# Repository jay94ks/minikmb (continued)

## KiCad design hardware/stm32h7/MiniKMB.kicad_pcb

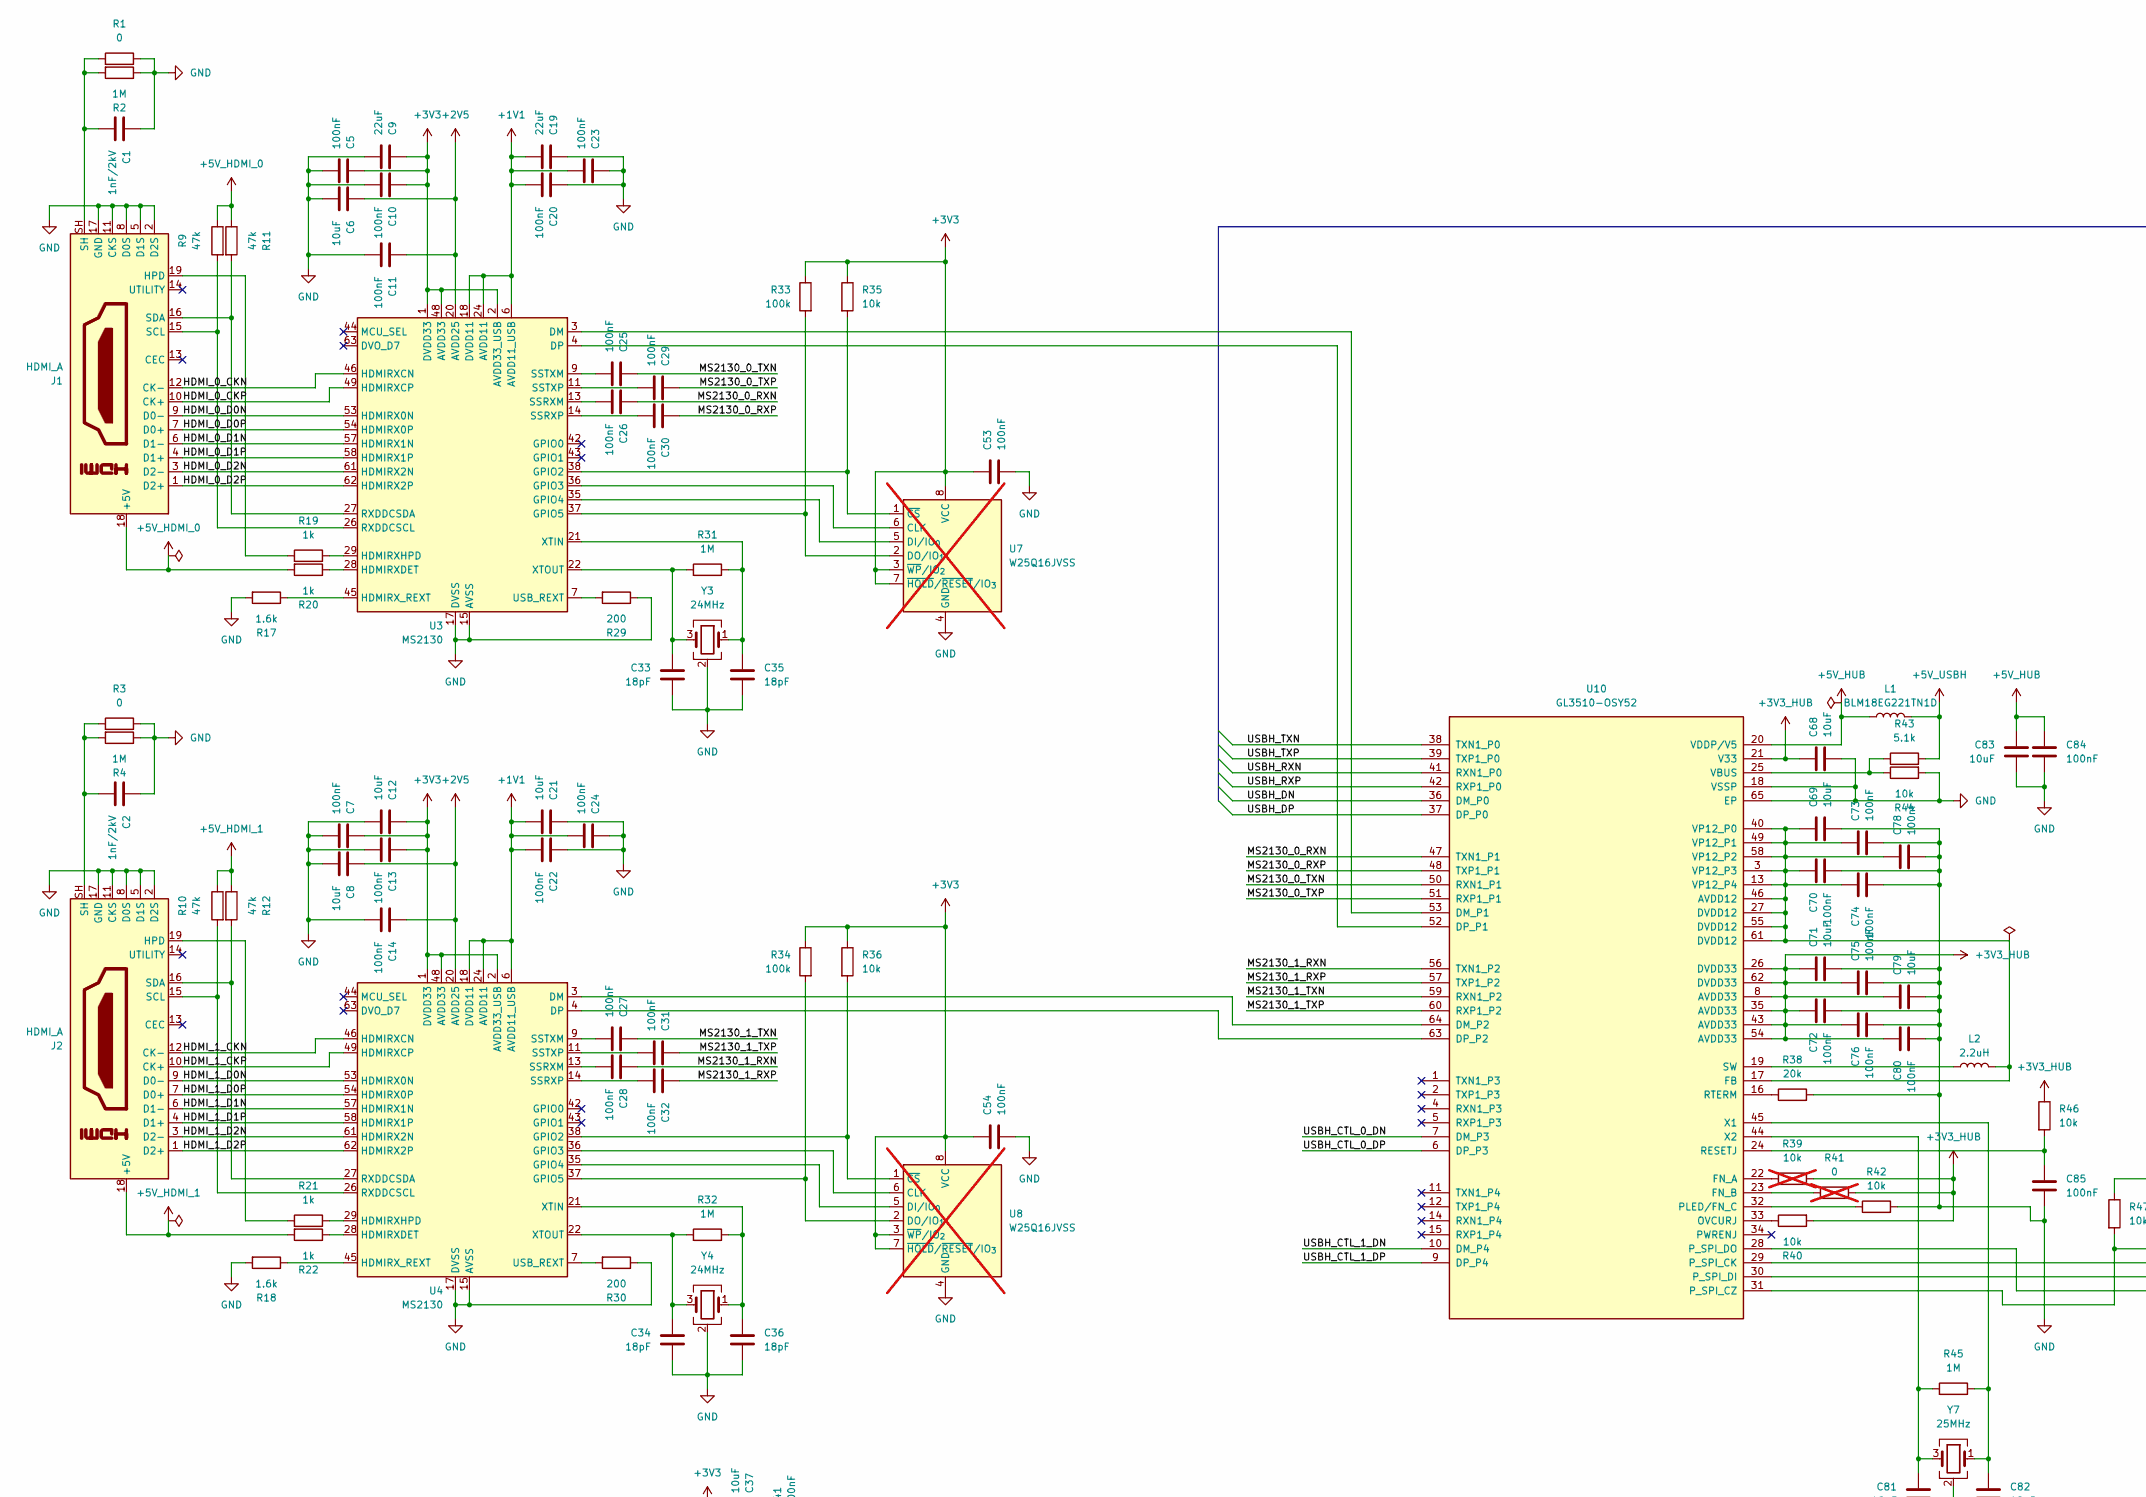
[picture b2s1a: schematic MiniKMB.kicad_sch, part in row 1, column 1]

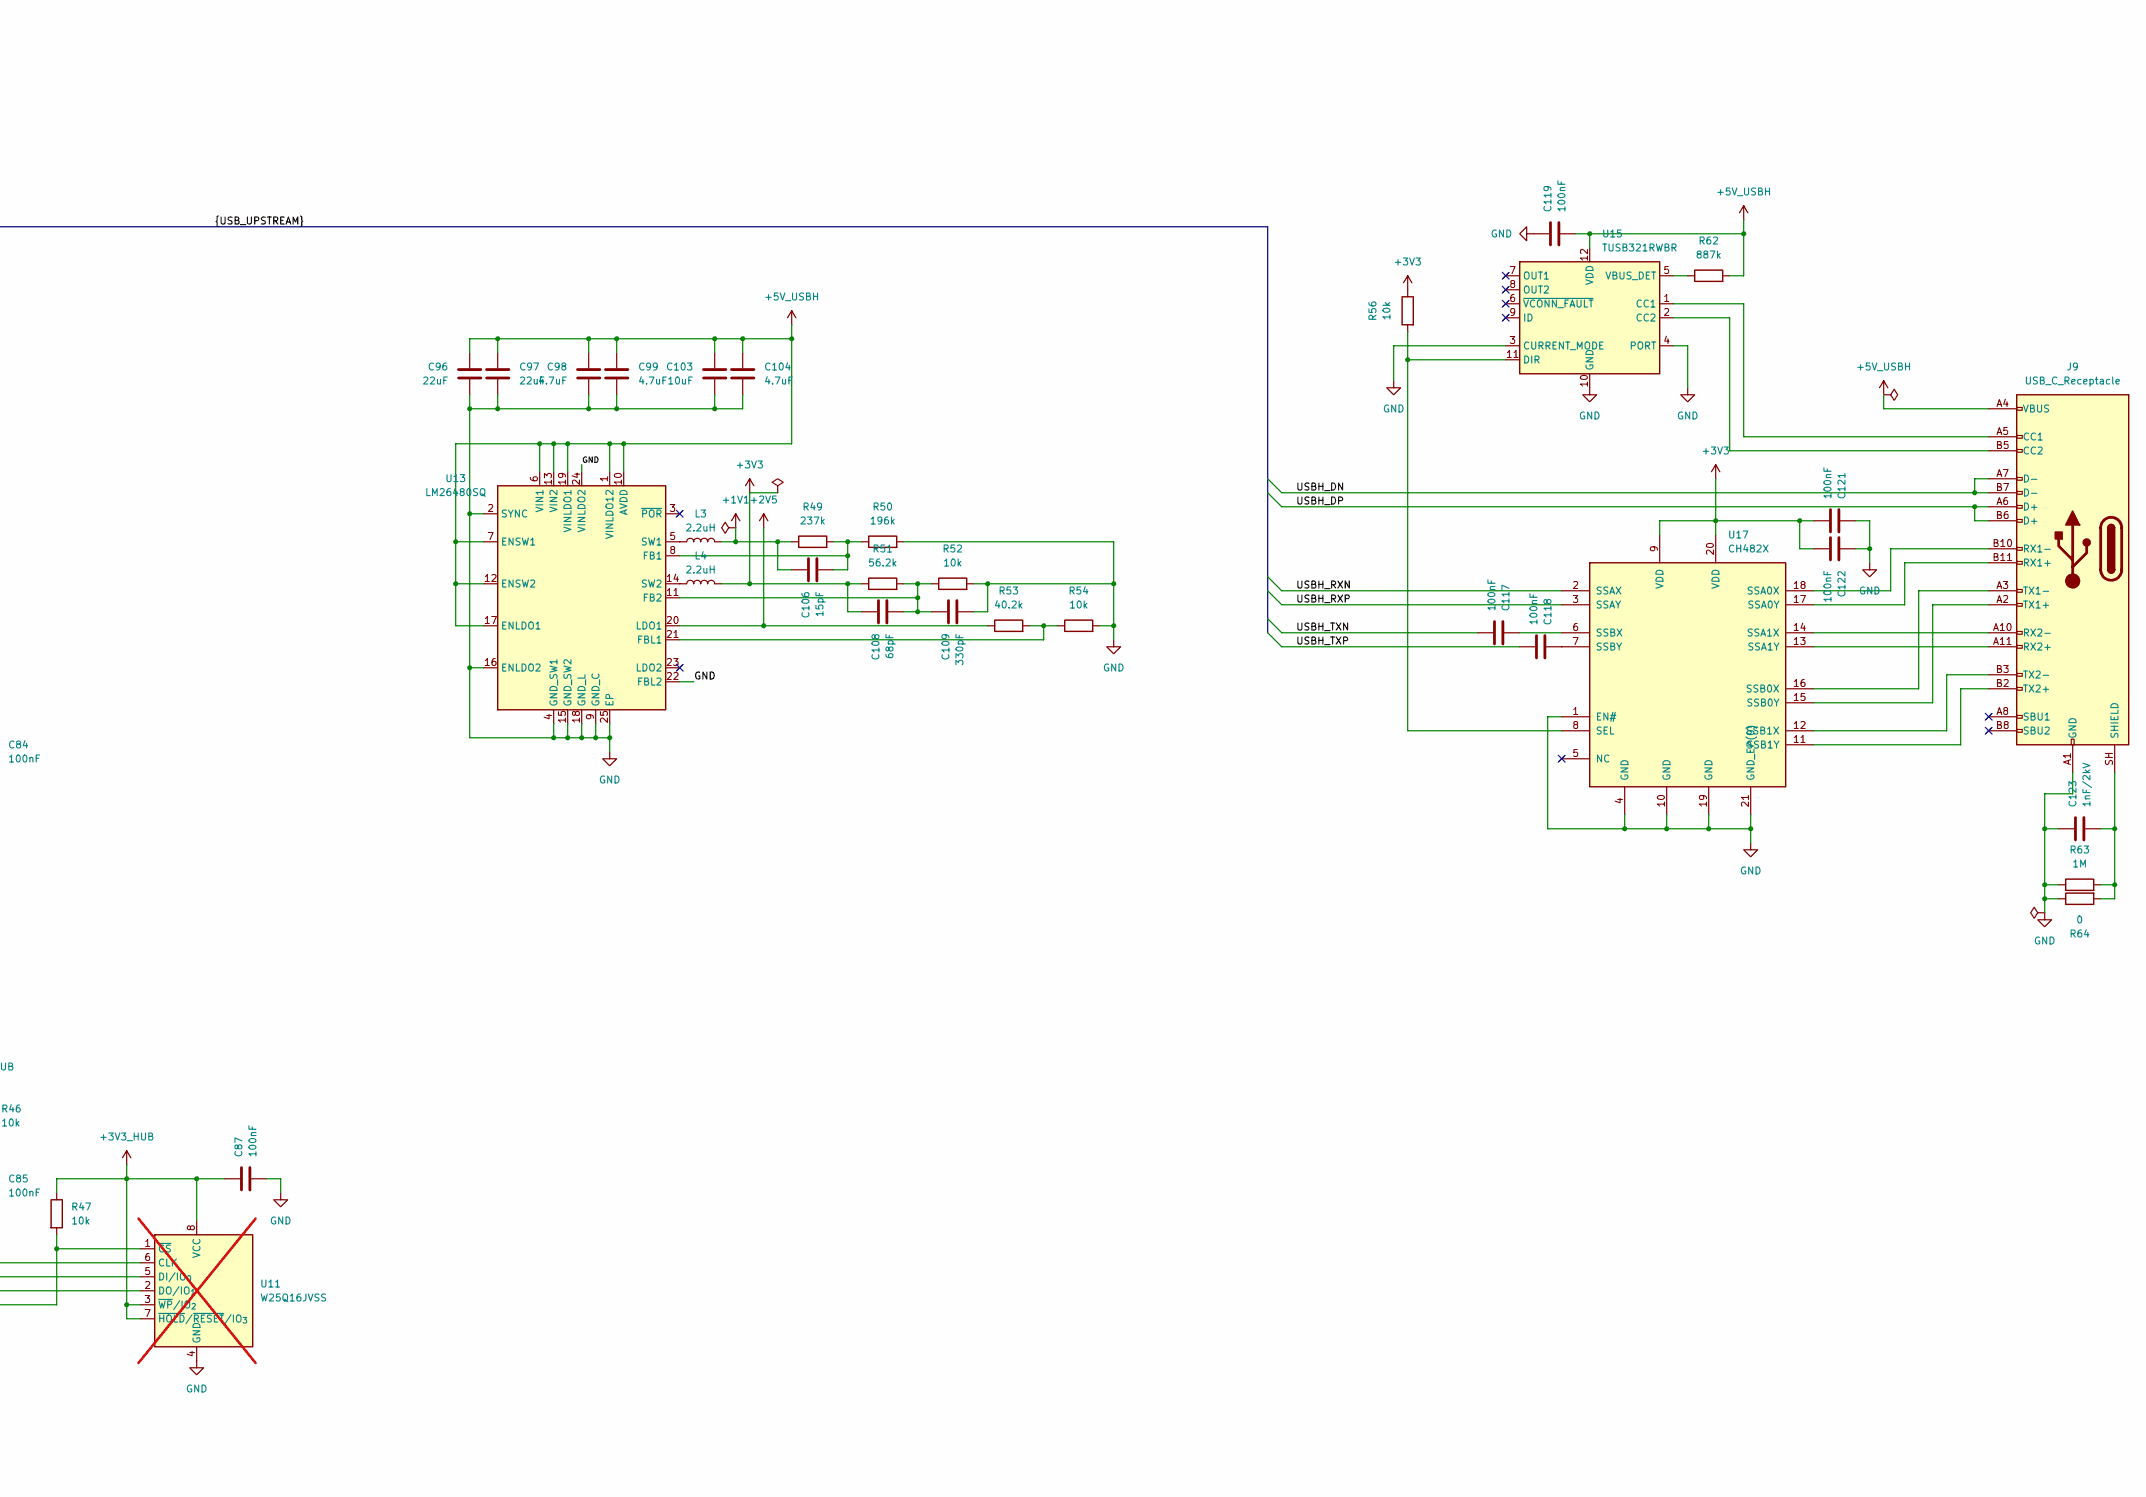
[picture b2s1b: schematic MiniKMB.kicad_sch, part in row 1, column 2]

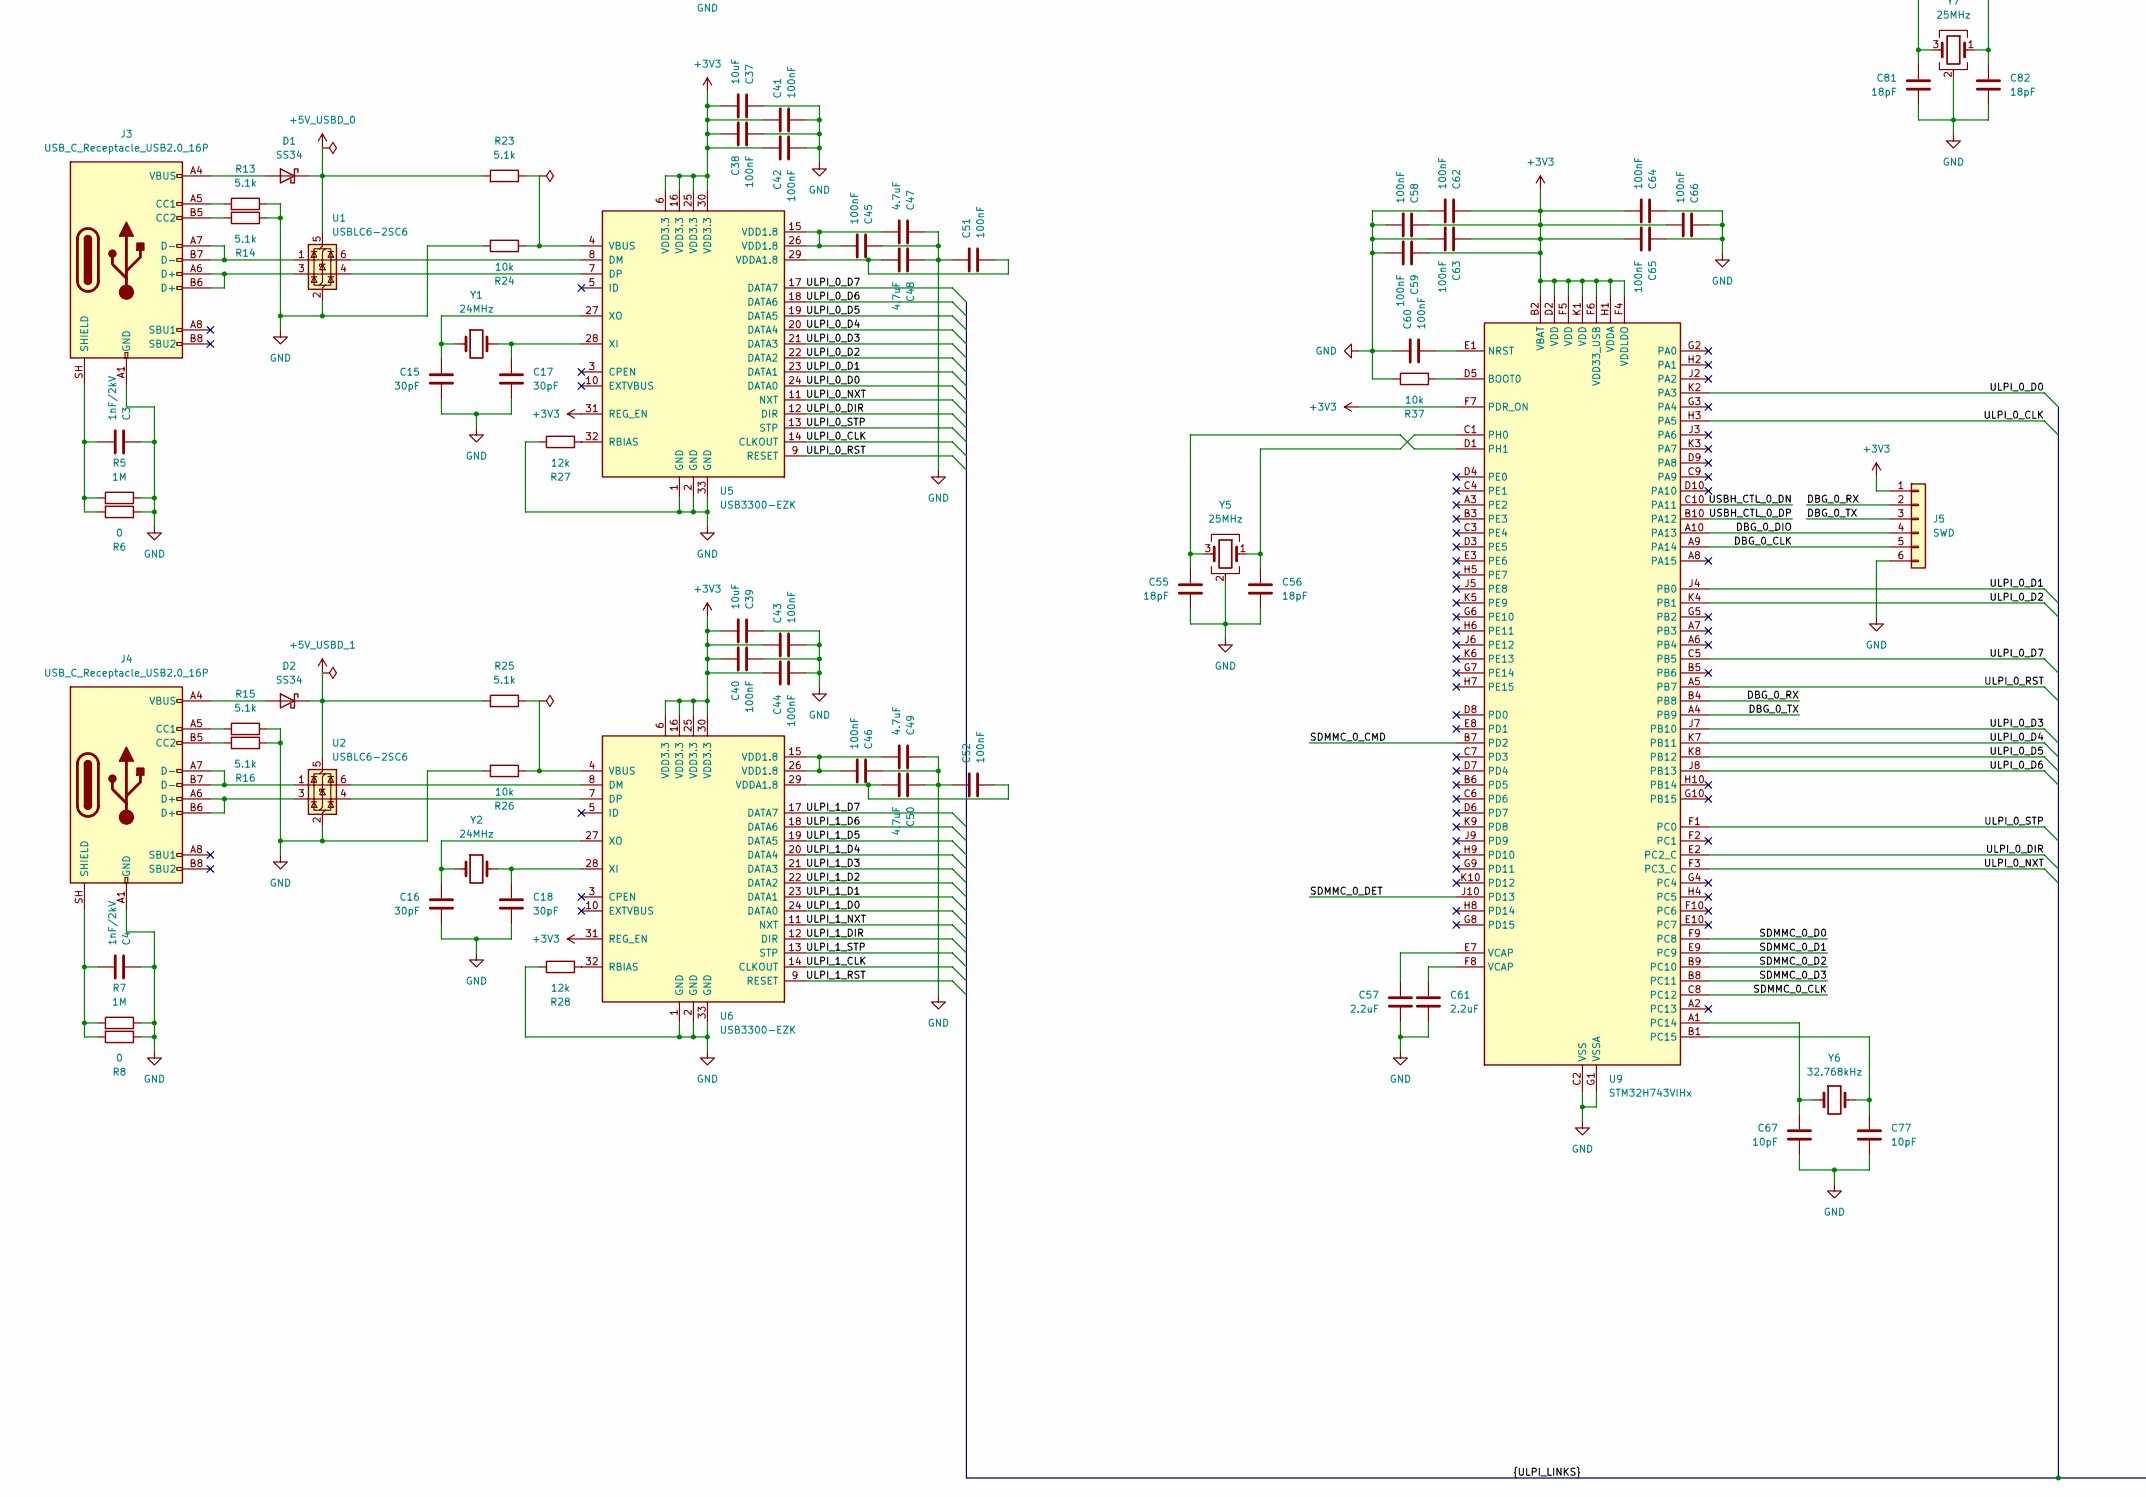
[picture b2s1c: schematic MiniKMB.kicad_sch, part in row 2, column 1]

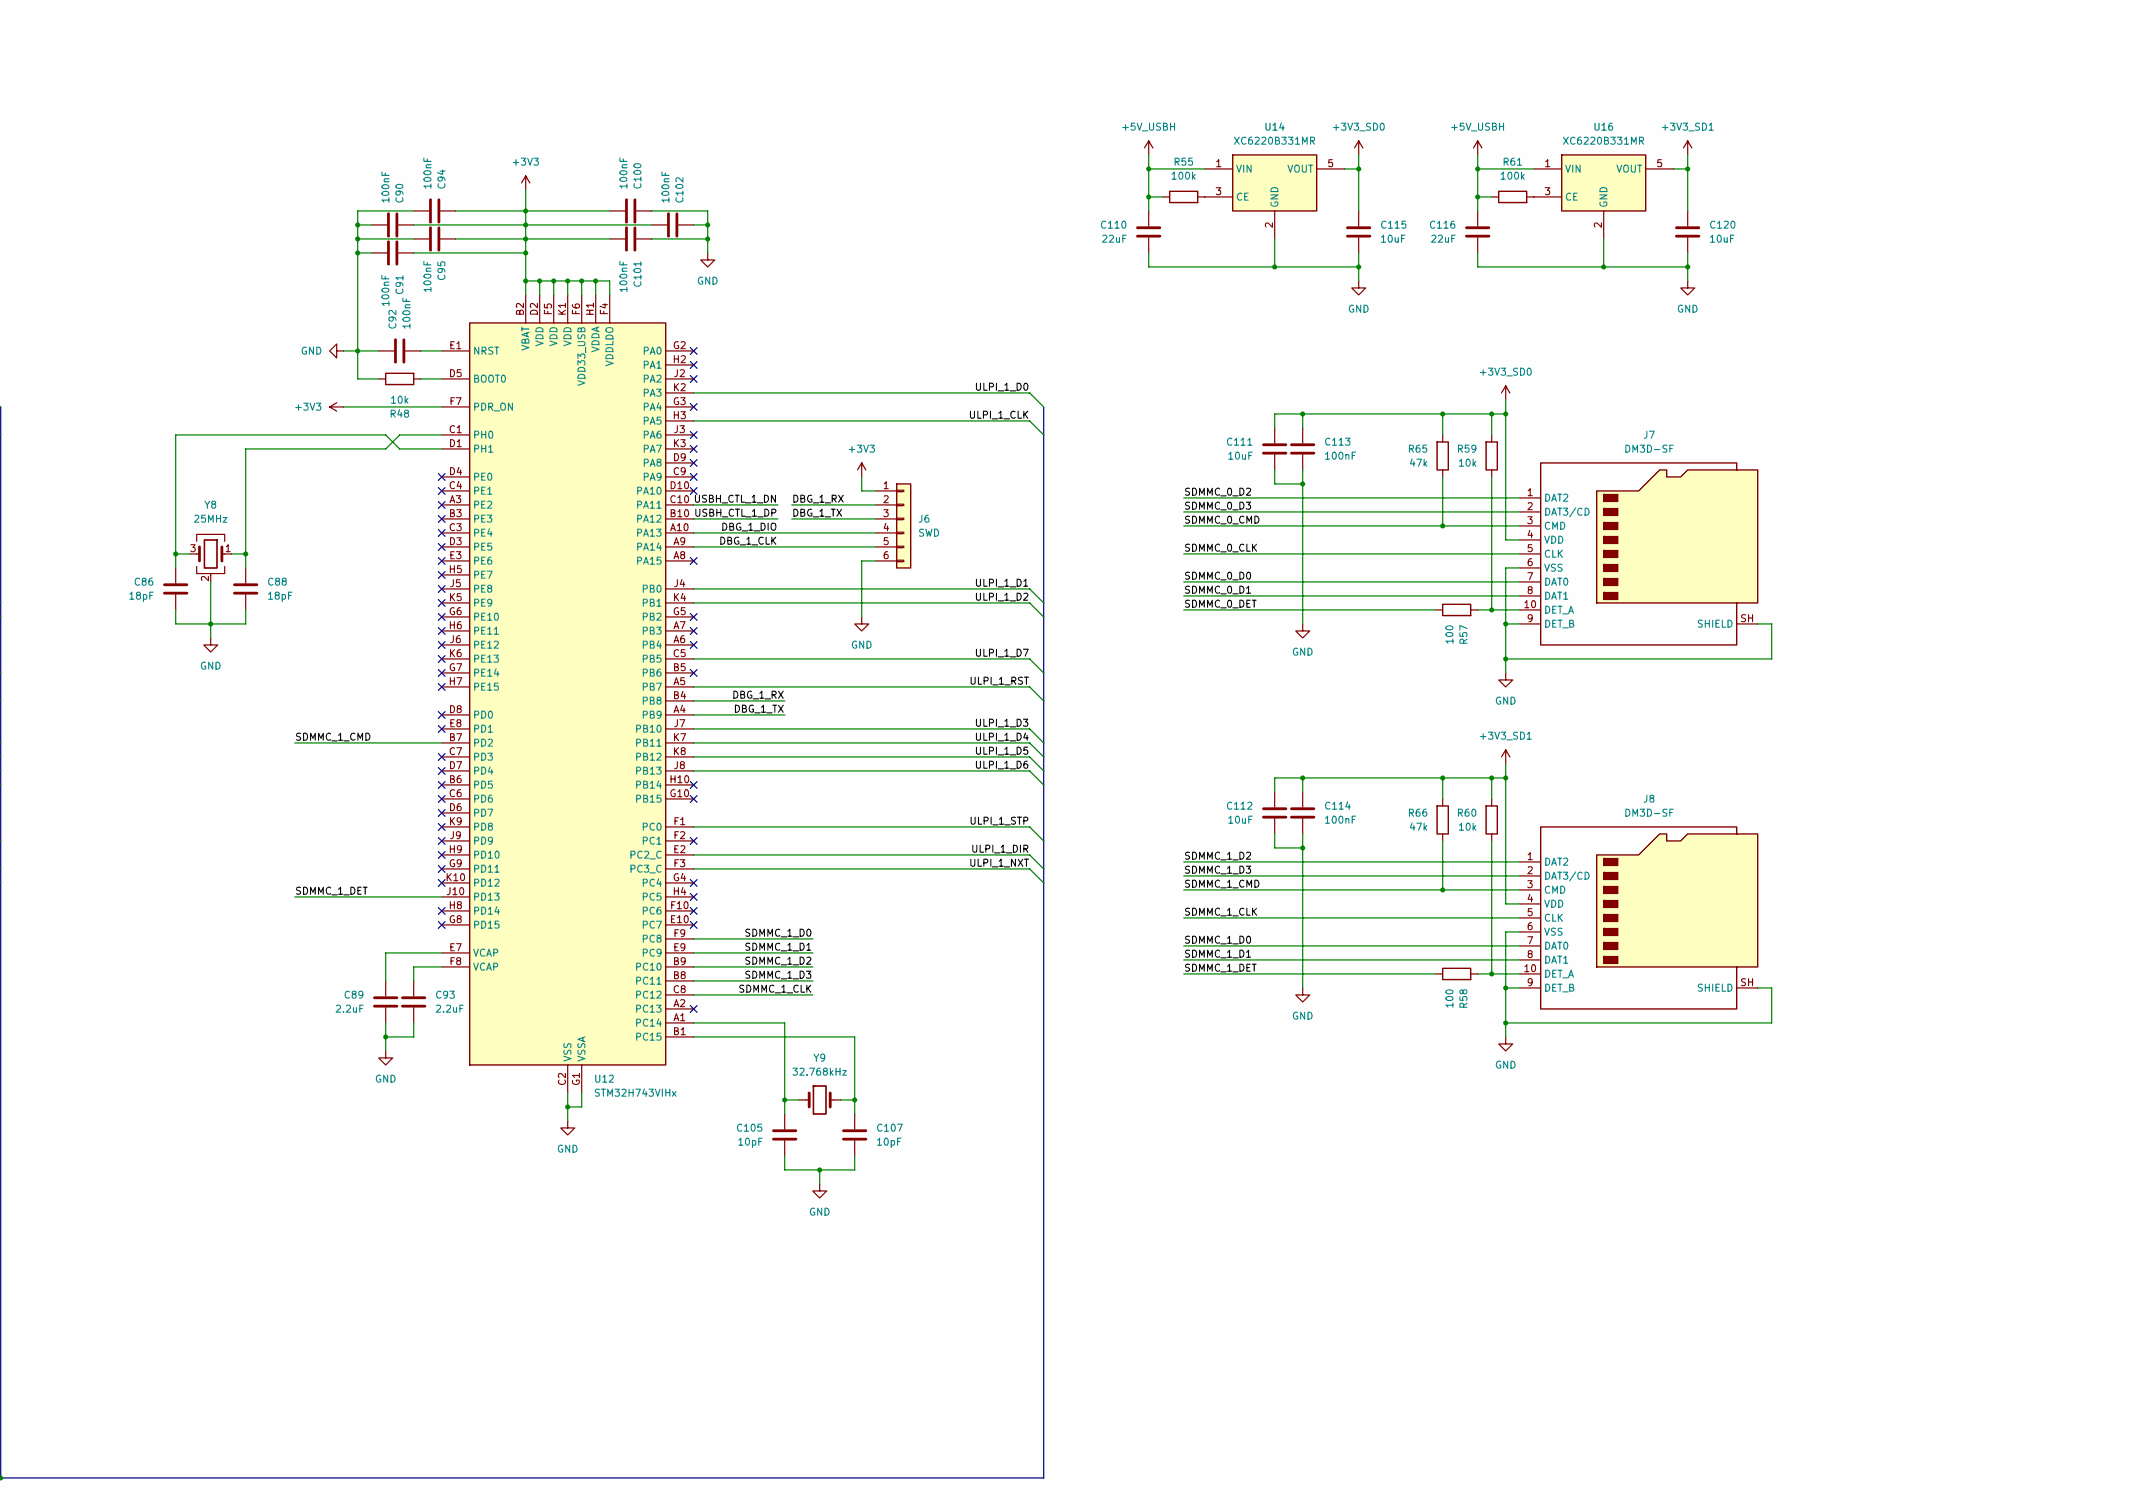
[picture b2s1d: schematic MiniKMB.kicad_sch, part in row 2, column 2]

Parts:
C1, C2, C3, C4, C123: 1nF/2kV; C_1206_3216Metric; Tolerance 10%; Voltage 2kV; MPN 1206B102K202NT; LCSC C9196
C5, C7, C10, C11, C13, C14, C20, C22, C23, C24, C25, C26, C27, C28, C29, C30, C31, C32, C38, C40, C41, C42, C43, C44, C45, C46, C51, C52, C53, C54, C58, C59, C60, C62, C63, C64, C65, C66, C70, C72, C73, C74, C75, C76, C78, C80, C84, C85, C87, C90, C91, C92, C94, C95, C100, C101, C102, C113, C114, C117, C118, C119, C121, C122: 100nF; C_0402_1005Metric; Tolerance 10%; Voltage 16V; MPN CL05B104KO5NNNC; LCSC C1525
C6, C12, C21, C37, C39, C68, C69, C71, C103, C111, C112, C120: 10uF; C_0603_1608Metric; Tolerance 20%; Voltage 25V; MPN CL10A106MA8NRNC; LCSC C96446
C8, C115: 10uF; C_0402_1005Metric; Tolerance 20%; Voltage 10V; MPN CL05A106MP6NUN8; LCSC C3902158
C9, C19: 22uF; C_0805_2012Metric; Tolerance 20%; Voltage 25V; MPN CL21A226MAQNNNE; LCSC C45783
C15, C16, C17, C18: 30pF; C_0402_1005Metric; MPN 0402CG300J500NT; LCSC C1570
C33, C34, C35, C36, C55, C56, C81, C82, C86, C88: 18pF; C_0402_1005Metric; MPN 0402CG180J500NT; LCSC C1549
C47, C48, C49, C50, C98, C99, C104: 4.7uF; C_0603_1608Metric; Tolerance 10%; Voltage 25V; MPN CL10A475KA8NQNC; LCSC C69335
C57, C61, C89, C93: 2.2uF; C_0603_1608Metric; Tolerance 10%; Voltage 10V; MPN CL10B225KP8NNNC; LCSC C100082
C67, C77, C105, C107: 10pF; C_0402_1005Metric; MPN 0402CG100J500NT; LCSC C1545
C79, C83: 10uF; C_0805_2012Metric; Tolerance 10%; Voltage 50V; MPN CL21A106KBYQNNE; LCSC C2932476
C96, C97: 22uF; C_1206_3216Metric; Tolerance 10%; Voltage 25V; MPN CL31A226KAHNNNE; LCSC C12891
C106: 15pF; C_0402_1005Metric; Tolerance 5%; Voltage 50V; MPN 0402CG150J500NT; LCSC C1548
C108: 68pF; C_0402_1005Metric; Tolerance 5%; Voltage 50V; MPN GRM1555C1H680JA01D; LCSC C76977
C109: 330pF; C_0402_1005Metric; Tolerance 5%; Voltage 50V; MPN GRM1555C1H331JA01D; LCSC C76965
C110, C116: 22uF; C_0805_2012Metric; Tolerance 20%; Voltage 25V; MPN CL21A226MAYNNNE; LCSC C602037
D1, D2: SS34; D_SMA; MPN SS34; LCSC C8678
J1, J2: HDMI_A; HDMI_A_Molex_208658-1001_Horizontal
J3, J4: USB_C_Receptacle_USB2.0_16P; USB_C_Receptacle_Palconn_UTC16-G; MPN TYPE-C-31-M-12; LCSC C165948
J5, J6: SWD; PinHeader_1x06_P2.54mm_Vertical; MPN PZ254V-11-06P; LCSC C492405
J7, J8: DM3D-SF; microSD_HC_Hirose_DM3D-SF; MPN DM3D-SF; LCSC C719027
J9: USB_C_Receptacle; USB_C_Receptacle_Amphenol_12401610E4-2A; MPN 12401610E4#2A; LCSC C5119948
L1: BLM18EG221TN1D; L_0603_1608Metric; MPN BLM18EG221TN1D; LCSC C113025
L2, L3, L4: 2.2uH; L_Sunlord_SWPA4020S; MPN SWPA4020S2R2MT; LCSC C83423
R1, R3, R6, R8, R64: 0; R_0805_2012Metric; Tolerance jumper; MPN 0805W8F0000T5E; LCSC C17477
R2, R4, R5, R7, R63: 1M; R_0805_2012Metric; Tolerance 1%; Voltage 150V; MPN 0805W8F1004T5E; LCSC C17514
R9, R10, R11, R12, R65, R66: 47k; R_0402_1005Metric; Tolerance 1%; Voltage 50V; MPN 0402WGF4702TCE; LCSC C25792
R13, R14, R15, R16, R23, R25, R43: 5.1k; R_0402_1005Metric; Tolerance 1%; Voltage 50V; MPN 0402WGF5101TCE; LCSC C25905
R17, R18: 1.6k; R_0402_1005Metric; Tolerance 1%; Voltage 50V; MPN 0402WGF1601TCE; LCSC C4908
R19, R20, R21, R22: 1k; R_0402_1005Metric; Tolerance 1%; Voltage 50V; MPN 0402WGF1001TCE; LCSC C11702
R24, R26, R35, R36, R37, R40, R42, R44, R46, R47, R48, R56, R59, R60: 10k; R_0402_1005Metric; Tolerance 1%; Voltage 50V; MPN 0402WGF1002TCE; LCSC C25744
R27, R28: 12k; R_0402_1005Metric; Tolerance 1%; Voltage 50V; MPN 0402WGF1202TCE; LCSC C25752
R29, R30: 200; R_0402_1005Metric; Tolerance 1%; Voltage 50V; MPN 0402WGF2000TCE; LCSC C25087
R31, R32, R45: 1M; R_0402_1005Metric; Tolerance 1%; Voltage 50V; MPN 0402WGF1004TCE; LCSC C26083
R33, R34, R55, R61: 100k; R_0402_1005Metric; Tolerance 1%; Voltage 50V; MPN 0402WGF1003TCE; LCSC C25741
R38: 20k; R_0402_1005Metric; Tolerance 1%; Voltage 50V; MPN 0402WGF2002TCE; LCSC C25765
R39: 10k; R_0402_1005Metric; not fitted
R41: 0; R_0402_1005Metric; not fitted
R49: 237k; R_0402_1005Metric; Tolerance 0.1%; Voltage 50V; MPN RT0402BRD07237KL; LCSC C852654
R50: 196k; R_0402_1005Metric; Tolerance 0.1%; Voltage 50V; MPN RT0402BRD07196KL; LCSC C852585
R51: 56.2k; R_0402_1005Metric; Tolerance 0.1%; Voltage 50V; MPN RT0402BRB0756K2L; LCSC C705626
R52, R54: 10k; R_0402_1005Metric; Tolerance 0.1%; Voltage 50V; MPN RT0402BRD0710KL; LCSC C190095
R53: 40.2k; R_0402_1005Metric; Tolerance 0.1%; Voltage 50V; MPN RT0402BRD0740K2L; LCSC C852775
R57, R58: 100; R_0402_1005Metric; Tolerance 1%; Voltage 50V; MPN 0402WGF1000TCE; LCSC C25076
R62: 887k; R_0402_1005Metric; Tolerance 1%; Voltage 50V; MPN 0402WGF8873TCE; LCSC C423127
U1, U2: USBLC6-2SC6; SOT-23-6; MPN USBLC6-2SC6; LCSC C7519
U3, U4: MS2130; QFN-64-1EP_9x9mm_P0.5mm_EP5.7x5.7mm; MPN MS2130; LCSC C5905137
U5, U6: USB3300-EZK; QFN-32-1EP_5x5mm_P0.5mm_EP3.45x3.45mm; MPN USB3300-EZK-TR; LCSC C108383
U7, U8, U11: W25Q16JVSS; SOIC-8_5.3x5.3mm_P1.27mm; not fitted
U9, U12: STM32H743VIHx; TFBGA-100_8x8mm_Layout10x10_P0.8mm; MPN STM32H743VIH6; LCSC C964146
U10: GL3510-OSY52; GL3510-OSY52_QFN-64-1EP_8x8mm_P0.4mm; MPN GL3510-OSY52; LCSC C7501408
U13: LM26480SQ; WQFN-24-1EP_4x4mm_P0.5mm_EP2.6x2.6mm; MPN LM26480SQ-AA/NOPB; LCSC C131997
U14, U16: XC6220B331MR; SOT-23-5; MPN XC6220B331MR-G; LCSC C86534
U15: TUSB321RWBR; Texas_X2QFN-12_1.6x1.6mm_P0.4mm; MPN TUSB321RWBR; LCSC C139392
U17: CH482X; CH482X_QFN-20-1EP_2.5x4.5mm_P0.5mm; MPN CH482X; LCSC C2913011
Y1, Y2: 24MHz; Crystal_SMD_HC49-SD; MPN X49SS2-24.000-F18LJDT; LCSC C2890201
Y3, Y4: 24MHz; Crystal_SMD_3225-4Pin_3.2x2.5mm; MPN X322524MOB4SI; LCSC C70590
Y5, Y7, Y8: 25MHz; Crystal_SMD_3225-4Pin_3.2x2.5mm; MPN X322525MOB4SI; LCSC C9006
Y6, Y9: 32.768kHz; Crystal_SMD_2012-2Pin_2.0x1.2mm; MPN X1A0000610006; LCSC C99009

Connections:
+1V1: C19.2, C20.2, C21.2, C22.2, C23.2, C24.2, C106.1, L3.2, R49.1, U3.6 (AVDD11_USB), U3.10 (AVDD11_USB), U3.12 (AVDD11_USB), U3.18 (DVDD11), U3.24 (AVDD11), U3.39 (DVDD11), U3.51 (AVDD11), U3.55 (AVDD11), U3.59 (AVDD11), U4.6 (AVDD11_USB), U4.10 (AVDD11_USB), U4.12 (AVDD11_USB), U4.18 (DVDD11), U4.24 (AVDD11), U4.39 (DVDD11), U4.51 (AVDD11), U4.55 (AVDD11), U4.59 (AVDD11)
+2V5: C6.1, C8.1, C11.1, C14.1, R53.1, U3.20 (AVDD25), U3.23 (AVDD25), U3.47 (AVDD25), U4.20 (AVDD25), U4.23 (AVDD25), U4.47 (AVDD25), U13.20 (LDO1)
+3V3: C5.1, C7.1, C9.1, C10.1, C12.1, C13.1, C37.2, C38.1, C39.2, C40.1, C41.1, C42.1, C43.1, C44.1, C53.1, C54.1, C58.1, C59.1, C62.1, C63.1, C64.2, C65.2, C66.2, C90.1, C91.1, C94.1, C95.1, C100.2, C101.2, C102.2, C108.1, C121.2, C122.2, J5.1, J6.1, L4.2, R33.1, R34.1, R35.1, R36.1, R51.1, R56.1, U3.1 (DVDD33), U3.2 (AVDD33_USB), U3.5 (AVDD33_USB), U3.8 (AVDD33_USB), U3.16 (DVDD33), U3.31 (DVDD33), U3.33 (DVDD33), U3.41 (DVDD33), U3.48 (AVDD33), U3.52 (AVDD33), U3.56 (AVDD33), U3.60 (AVDD33), U4.1 (DVDD33), U4.2 (AVDD33_USB), U4.5 (AVDD33_USB), U4.8 (AVDD33_USB), U4.16 (DVDD33), U4.31 (DVDD33), U4.33 (DVDD33), U4.41 (DVDD33), U4.48 (AVDD33), U4.52 (AVDD33), U4.56 (AVDD33), U4.60 (AVDD33), U5.6 (VDD3.3), U5.16 (VDD3.3), U5.25 (VDD3.3), U5.30 (VDD3.3), U5.31 (REG_EN), U6.6 (VDD3.3), U6.16 (VDD3.3), U6.25 (VDD3.3), U6.30 (VDD3.3), U6.31 (REG_EN), U7.3 (~WP/IO_{2}), U7.7 (~HOLD/~RESET/IO_{3}), U7.8 (VCC), U8.3 (~WP/IO_{2}), U8.7 (~HOLD/~RESET/IO_{3}), U8.8 (VCC), U9.B2 (VBAT), U9.D2 (VDD), U9.F4 (VDDLDO), U9.F5 (VDD), U9.F6 (VDD33_USB), U9.F7 (PDR_ON), U9.H1 (VDDA), U9.K1 (VDD), U12.B2 (VBAT), U12.D2 (VDD), U12.F4 (VDDLDO), U12.F5 (VDD), U12.F6 (VDD33_USB), U12.F7 (PDR_ON), U12.H1 (VDDA), U12.K1 (VDD), U17.9 (VDD), U17.20 (VDD)
+3V3_HUB: C68.1, C71.1, C72.1, C75.1, C76.1, C79.1, C80.1, C87.1, R39.2, R40.2, R41.2, R46.1, R47.1, U10.8 (AVDD33), U10.21 (V33), U10.26 (DVDD33), U10.35 (AVDD33), U10.43 (AVDD33), U10.54 (AVDD33), U10.62 (DVDD33), U11.3 (~WP/IO_{2}), U11.7 (~HOLD/~RESET/IO_{3}), U11.8 (VCC)
+3V3_SD0: C111.1, C113.1, C115.1, J7.4 (VDD), R59.2, R65.2, U14.5 (VOUT)
+3V3_SD1: C112.1, C114.1, C120.1, J8.4 (VDD), R60.2, R66.2, U16.5 (VOUT)
+5V_HDMI_0: J1.18 (+5V), R9.1, R11.1, R20.2
+5V_HDMI_1: J2.18 (+5V), R10.1, R12.1, R22.2
+5V_HUB: C83.1, C84.1, L1.1, U10.20 (VDDP/V5)
+5V_USBD_0: D1.1 (K), R23.2, U1.5 (VBUS)
+5V_USBD_1: D2.1 (K), R25.2, U2.5 (VBUS)
+5V_USBH: C96.1, C97.1, C98.1, C99.1, C103.1, C104.1, C110.1, C116.1, C119.2, J9.A4 (VBUS), J9.A9 (VBUS), J9.B4 (VBUS), J9.B9 (VBUS), L1.2, R43.2, R55.1, R61.1, R62.2, U13.1 (VINLDO12), U13.6 (VIN1), U13.7 (ENSW1), U13.10 (AVDD), U13.12 (ENSW2), U13.13 (VIN2), U13.17 (ENLDO1), U13.19 (VINLDO1), U14.1 (VIN), U15.12 (VDD), U16.1 (VIN)
/DBG_0_CLK: J5.5, U9.A9 (PA14)
/DBG_0_DIO: J5.4, U9.A10 (PA13)
/DBG_0_RX: J5.2, U9.B4 (PB8)
/DBG_0_TX: J5.3, U9.A4 (PB9)
/DBG_1_CLK: J6.5, U12.A9 (PA14)
/DBG_1_DIO: J6.4, U12.A10 (PA13)
/DBG_1_RX: J6.2, U12.B4 (PB8)
/DBG_1_TX: J6.3, U12.A4 (PB9)
/HDMI_0_CKN: J1.12 (CK-), U3.46 (HDMIRXCN)
/HDMI_0_CKP: J1.10 (CK+), U3.49 (HDMIRXCP)
/HDMI_0_D0N: J1.9 (D0-), U3.53 (HDMIRX0N)
/HDMI_0_D0P: J1.7 (D0+), U3.54 (HDMIRX0P)
/HDMI_0_D1N: J1.6 (D1-), U3.57 (HDMIRX1N)
/HDMI_0_D1P: J1.4 (D1+), U3.58 (HDMIRX1P)
/HDMI_0_D2N: J1.3 (D2-), U3.61 (HDMIRX2N)
/HDMI_0_D2P: J1.1 (D2+), U3.62 (HDMIRX2P)
/HDMI_1_CKN: J2.12 (CK-), U4.46 (HDMIRXCN)
/HDMI_1_CKP: J2.10 (CK+), U4.49 (HDMIRXCP)
/HDMI_1_D0N: J2.9 (D0-), U4.53 (HDMIRX0N)
/HDMI_1_D0P: J2.7 (D0+), U4.54 (HDMIRX0P)
/HDMI_1_D1N: J2.6 (D1-), U4.57 (HDMIRX1N)
/HDMI_1_D1P: J2.4 (D1+), U4.58 (HDMIRX1P)
/HDMI_1_D2N: J2.3 (D2-), U4.61 (HDMIRX2N)
/HDMI_1_D2P: J2.1 (D2+), U4.62 (HDMIRX2P)
/MS2130_0_RXN: C26.1, U10.47 (TXN1_P1)
/MS2130_0_RXP: C30.1, U10.48 (TXP1_P1)
/MS2130_0_TXN: C25.1, U10.50 (RXN1_P1)
/MS2130_0_TXP: C29.1, U10.51 (RXP1_P1)
/MS2130_1_RXN: C28.1, U10.56 (TXN1_P2)
/MS2130_1_RXP: C32.1, U10.57 (TXP1_P2)
/MS2130_1_TXN: C27.1, U10.59 (RXN1_P2)
/MS2130_1_TXP: C31.1, U10.60 (RXP1_P2)
/SDMMC_0_CLK: J7.5 (CLK), U9.C8 (PC12)
/SDMMC_0_CMD: J7.3 (CMD), R65.1, U9.B7 (PD2)
/SDMMC_0_D0: J7.7 (DAT0), U9.F9 (PC8)
/SDMMC_0_D1: J7.8 (DAT1), U9.E9 (PC9)
/SDMMC_0_D2: J7.1 (DAT2), U9.B9 (PC10)
/SDMMC_0_D3: J7.2 (DAT3/CD), U9.B8 (PC11)
/SDMMC_0_DET: R57.1, U9.J10 (PD13)
/SDMMC_1_CLK: J8.5 (CLK), U12.C8 (PC12)
/SDMMC_1_CMD: J8.3 (CMD), R66.1, U12.B7 (PD2)
/SDMMC_1_D0: J8.7 (DAT0), U12.F9 (PC8)
/SDMMC_1_D1: J8.8 (DAT1), U12.E9 (PC9)
/SDMMC_1_D2: J8.1 (DAT2), U12.B9 (PC10)
/SDMMC_1_D3: J8.2 (DAT3/CD), U12.B8 (PC11)
/SDMMC_1_DET: R58.1, U12.J10 (PD13)
/ULPI_0_CLK: U5.14 (CLKOUT), U9.H3 (PA5)
/ULPI_0_D0: U5.24 (DATA0), U9.K2 (PA3)
/ULPI_0_D1: U5.23 (DATA1), U9.J4 (PB0)
/ULPI_0_D2: U5.22 (DATA2), U9.K4 (PB1)
/ULPI_0_D3: U5.21 (DATA3), U9.J7 (PB10)
/ULPI_0_D4: U5.20 (DATA4), U9.K7 (PB11)
/ULPI_0_D5: U5.19 (DATA5), U9.K8 (PB12)
/ULPI_0_D6: U5.18 (DATA6), U9.J8 (PB13)
/ULPI_0_D7: U5.17 (DATA7), U9.C5 (PB5)
/ULPI_0_DIR: U5.12 (DIR), U9.E2 (PC2_C)
/ULPI_0_NXT: U5.11 (NXT), U9.F3 (PC3_C)
/ULPI_0_RST: U5.9 (RESET), U9.A5 (PB7)
/ULPI_0_STP: U5.13 (STP), U9.F1 (PC0)
/ULPI_1_CLK: U6.14 (CLKOUT), U12.H3 (PA5)
/ULPI_1_D0: U6.24 (DATA0), U12.K2 (PA3)
/ULPI_1_D1: U6.23 (DATA1), U12.J4 (PB0)
/ULPI_1_D2: U6.22 (DATA2), U12.K4 (PB1)
/ULPI_1_D3: U6.21 (DATA3), U12.J7 (PB10)
/ULPI_1_D4: U6.20 (DATA4), U12.K7 (PB11)
/ULPI_1_D5: U6.19 (DATA5), U12.K8 (PB12)
/ULPI_1_D6: U6.18 (DATA6), U12.J8 (PB13)
/ULPI_1_D7: U6.17 (DATA7), U12.C5 (PB5)
/ULPI_1_DIR: U6.12 (DIR), U12.E2 (PC2_C)
/ULPI_1_NXT: U6.11 (NXT), U12.F3 (PC3_C)
/ULPI_1_RST: U6.9 (RESET), U12.A5 (PB7)
/ULPI_1_STP: U6.13 (STP), U12.F1 (PC0)
/USBH_CTL_0_DN: U9.C10 (PA11), U10.7 (DM_P3)
/USBH_CTL_0_DP: U9.B10 (PA12), U10.6 (DP_P3)
/USBH_CTL_1_DN: U10.10 (DM_P4), U12.C10 (PA11)
/USBH_CTL_1_DP: U10.9 (DP_P4), U12.B10 (PA12)
/USBH_DN: J9.A7 (D-), J9.B7 (D-), U10.36 (DM_P0)
/USBH_DP: J9.A6 (D+), J9.B6 (D+), U10.37 (DP_P0)
/USBH_RXN: U10.41 (RXN1_P0), U17.2 (SSAX)
/USBH_RXP: U10.42 (RXP1_P0), U17.3 (SSAY)
/USBH_TXN: C117.2, U10.38 (TXN1_P0)
/USBH_TXP: C118.2, U10.39 (TXP1_P0)
GND: C1.1, C2.1, C3.1, C4.1, C5.2, C6.2, C7.2, C8.2, C9.2, C10.2, C11.2, C12.2, C13.2, C14.2, C15.2, C16.2, C17.2, C18.2, C19.1, C20.1, C21.1, C22.1, C23.1, C24.1, C33.2, C34.2, C35.2, C36.2, C37.1, C38.2, C39.1, C40.2, C41.2, C42.2, C43.2, C44.2, C45.1, C46.1, C47.1, C48.1, C49.1, C50.1, C51.1, C52.1, C53.2, C54.2, C55.2, C56.2, C57.2, C58.2, C59.2, C60.1, C61.2, C62.2, C63.2, C64.1, C65.1, C66.1, C67.2, C68.2, C69.2, C70.2, C71.2, C72.2, C73.2, C74.2, C75.2, C76.2, C77.2, C78.2, C79.2, C80.2, C81.2, C82.2, C83.2, C84.2, C85.2, C86.2, C87.2, C88.2, C89.2, C90.2, C91.2, C92.1, C93.2, C94.2, C95.2, C96.2, C97.2, C98.2, C99.2, C100.1, C101.1, C102.1, C103.2, C104.2, C105.2, C107.2, C109.2, C110.2, C111.2, C112.2, C113.2, C114.2, C115.2, C116.2, C119.1, C120.2, C121.1, C122.1, C123.1, J1.2 (D2S), J1.5 (D1S), J1.8 (D0S), J1.11 (CKS), J1.17 (GND), J2.2 (D2S), J2.5 (D1S), J2.8 (D0S), J2.11 (CKS), J2.17 (GND), J3.A1 (GND), J3.A12 (GND), J3.B1 (GND), J3.B12 (GND), J4.A1 (GND), J4.A12 (GND), J4.B1 (GND), J4.B12 (GND), J5.6, J6.6, J7.6 (VSS), J7.9 (DET_B), J7.SH (SHIELD), J8.6 (VSS), J8.9 (DET_B), J8.SH (SHIELD), J9.A1 (GND), J9.A12 (GND), J9.B1 (GND), J9.B12 (GND), R1.1, R2.1, R3.1, R4.1, R5.1, R6.1, R7.1, R8.1, R13.1, R14.1, R15.1, R16.1, R17.2, R18.2, R24.2, R26.2, R27.1, R28.1, R29.1, R30.1, R37.1, R38.2, R42.2, R44.2, R48.1, R50.2, R52.2, R54.2, R63.1, R64.1, U1.2 (GND), U2.2 (GND), U3.15 (AVSS), U3.17 (DVSS), U3.19 (AVSS), U3.25 (AVSS), U3.30 (DVSS), U3.32 (DVSS), U3.34 (DVSS), U3.40 (DVSS), U3.50 (AVSS), U3.64 (DVSS), U3.65 (AVSS), U4.15 (AVSS), U4.17 (DVSS), U4.19 (AVSS), U4.25 (AVSS), U4.30 (DVSS), U4.32 (DVSS), U4.34 (DVSS), U4.40 (DVSS), U4.50 (AVSS), U4.64 (DVSS), U4.65 (AVSS), U5.1 (GND), U5.2 (GND), U5.33 (GND), U6.1 (GND), U6.2 (GND), U6.33 (GND), U7.4 (GND), U8.4 (GND), U9.C2 (VSS), U9.E4 (VSS), U9.E5 (VSS), U9.E6 (VSS), U9.G1 (VSSA), U9.J1 (VSS), U10.18 (VSSP), U10.65 (EP), U11.4 (GND), U12.C2 (VSS), U12.E4 (VSS), U12.E5 (VSS), U12.E6 (VSS), U12.G1 (VSSA), U12.J1 (VSS), U13.2 (SYNC), U13.4 (GND_SW1), U13.9 (GND_C), U13.15 (GND_SW2), U13.16 (ENLDO2), U13.18 (GND_L), U13.22 (FBL2), U13.24 (VINLDO2), U13.25 (EP), U14.2 (GND), U15.3 (CURRENT_MODE)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
unnamed: C1.2, J1.SH, R1.2, R2.2
unnamed: C2.2, J2.SH, R3.2, R4.2
unnamed: C45.2, C47.2, U5.15 (VDD1.8), U5.26 (VDD1.8)
unnamed: C46.2, C49.2, U6.15 (VDD1.8), U6.26 (VDD1.8)
unnamed: C57.1, U9.E7 (VCAP)
unnamed: C61.1, U9.F8 (VCAP)
unnamed: C89.1, U12.E7 (VCAP)
unnamed: C93.1, U12.F8 (VCAP)
unnamed: D1.2 (A), J3.A4 (VBUS), J3.A9 (VBUS), J3.B4 (VBUS), J3.B9 (VBUS)
unnamed: D2.2 (A), J4.A4 (VBUS), J4.A9 (VBUS), J4.B4 (VBUS), J4.B9 (VBUS)
unnamed: J1.19 (HPD), R19.2
unnamed: J1.15 (SCL), R9.2, U3.26 (RXDDCSCL)
unnamed: J1.16 (SDA), R11.2, U3.27 (RXDDCSDA)
unnamed: J2.19 (HPD), R21.2
unnamed: J2.15 (SCL), R10.2, U4.26 (RXDDCSCL)
unnamed: J2.16 (SDA), R12.2, U4.27 (RXDDCSDA)
unnamed: J3.A5 (CC1), R13.2
unnamed: J3.B5 (CC2), R14.2
unnamed: J3.A6 (D+), J3.B6 (D+), U1.3 (I/O2)
unnamed: J3.A7 (D-), J3.B7 (D-), U1.1 (I/O1)
unnamed: C3.2, J3.SH (SHIELD), R5.2, R6.2
unnamed: J4.A5 (CC1), R15.2
unnamed: J4.B5 (CC2), R16.2
unnamed: J4.A6 (D+), J4.B6 (D+), U2.3 (I/O2)
unnamed: J4.A7 (D-), J4.B7 (D-), U2.1 (I/O1)
unnamed: C4.2, J4.SH (SHIELD), R7.2, R8.2
unnamed: J7.10 (DET_A), R57.2, R59.1
unnamed: J8.10 (DET_A), R58.2, R60.1
unnamed: J9.A5 (CC1), U15.1 (CC1)
unnamed: J9.B5 (CC2), U15.2 (CC2)
unnamed: J9.B11 (RX1+), U17.17 (SSA0Y)
unnamed: J9.B10 (RX1-), U17.18 (SSA0X)
unnamed: J9.A11 (RX2+), U17.13 (SSA1Y)
unnamed: J9.A10 (RX2-), U17.14 (SSA1X)
unnamed: C123.2, J9.SH (SHIELD), R63.2, R64.2
unnamed: J9.A2 (TX1+), U17.15 (SSB0Y)
unnamed: J9.A3 (TX1-), U17.16 (SSB0X)
unnamed: J9.B2 (TX2+), U17.11 (SSB1Y)
unnamed: J9.B3 (TX2-), U17.12 (SSB1X)
unnamed: R35.2, U3.38 (GPIO2), U7.1 (~CS)
unnamed: U3.36 (GPIO3), U7.6 (CLK)
unnamed: U3.35 (GPIO4), U7.5 (DI/IO_{0})
unnamed: R33.2, U3.37 (GPIO5), U7.2 (DO/IO_{1})
unnamed: R20.1, U3.28 (HDMIRXDET)
unnamed: R19.1, U3.29 (HDMIRXHPD)
unnamed: R17.1, U3.45 (HDMIRX_REXT)
unnamed: C26.2, U3.13 (SSRXM)
unnamed: C30.2, U3.14 (SSRXP)
unnamed: C25.2, U3.9 (SSTXM)
unnamed: C29.2, U3.11 (SSTXP)
unnamed: R29.2, U3.7 (USB_REXT)
unnamed: C35.1, R31.1, U3.21 (XTIN), Y3.1
unnamed: C33.1, R31.2, U3.22 (XTOUT), Y3.3
unnamed: R36.2, U4.38 (GPIO2), U8.1 (~CS)
unnamed: U4.36 (GPIO3), U8.6 (CLK)
unnamed: U4.35 (GPIO4), U8.5 (DI/IO_{0})
unnamed: R34.2, U4.37 (GPIO5), U8.2 (DO/IO_{1})
unnamed: R22.1, U4.28 (HDMIRXDET)
unnamed: R21.1, U4.29 (HDMIRXHPD)
unnamed: R18.1, U4.45 (HDMIRX_REXT)
unnamed: C28.2, U4.13 (SSRXM)
unnamed: C32.2, U4.14 (SSRXP)
unnamed: C27.2, U4.9 (SSTXM)
unnamed: C31.2, U4.11 (SSTXP)
unnamed: R30.2, U4.7 (USB_REXT)
unnamed: C36.1, R32.1, U4.21 (XTIN), Y4.1
unnamed: C34.1, R32.2, U4.22 (XTOUT), Y4.3
unnamed: U1.6 (I/O1), U5.8 (DM)
unnamed: U1.4 (I/O2), U5.7 (DP)
unnamed: R27.2, U5.32 (RBIAS)
unnamed: R23.1, R24.1, U5.4 (VBUS)
unnamed: C48.2, C51.2, U5.29 (VDDA1.8)
unnamed: C17.1, U5.28 (XI), Y1.2
unnamed: C15.1, U5.27 (XO), Y1.1
unnamed: U2.6 (I/O1), U6.8 (DM)
unnamed: U2.4 (I/O2), U6.7 (DP)
unnamed: R28.2, U6.32 (RBIAS)
unnamed: R25.1, R26.1, U6.4 (VBUS)
unnamed: C50.2, C52.2, U6.29 (VDDA1.8)
unnamed: C18.1, U6.28 (XI), Y2.2
unnamed: C16.1, U6.27 (XO), Y2.1
unnamed: R37.2, U9.D5 (BOOT0)
unnamed: C60.2, U9.E1 (NRST)
unnamed: C67.1, U9.A1 (PC14), Y6.1
unnamed: C77.1, U9.B1 (PC15), Y6.2
unnamed: C56.1, U9.C1 (PH0), Y5.1
unnamed: C55.1, U9.D1 (PH1), Y5.3
unnamed: C69.1, C70.1, C73.1, C74.1, C78.1, L2.2, U10.3 (VP12_P3), U10.13 (VP12_P4), U10.17 (FB), U10.27 (DVDD12), U10.40 (VP12_P0), U10.46 (AVDD12), U10.49 (VP12_P1), U10.55 (DVDD12), U10.58 (VP12_P2), U10.61 (DVDD12)
unnamed: U3.3 (DM), U10.53 (DM_P1)
unnamed: U4.3 (DM), U10.64 (DM_P2)
unnamed: U3.4 (DP), U10.52 (DP_P1)
unnamed: U4.4 (DP), U10.63 (DP_P2)
unnamed: R39.1, U10.22 (FN_A)
unnamed: R41.1, U10.23 (FN_B)
unnamed: R40.1, U10.33 (OVCURJ)
unnamed: R42.1, U10.32 (PLED/FN_C)
unnamed: U10.29 (P_SPI_CK), U11.6 (CLK)
unnamed: R47.2, U10.31 (P_SPI_CZ), U11.1 (~CS)
unnamed: U10.30 (P_SPI_DI), U11.5 (DI/IO_{0})
unnamed: U10.28 (P_SPI_DO), U11.2 (DO/IO_{1})
unnamed: C85.1, R46.2, U10.24 (RESETJ)
unnamed: R38.1, U10.16 (RTERM)
unnamed: L2.1, U10.19 (SW)
unnamed: R43.1, R44.1, U10.25 (VBUS)
unnamed: C82.1, R45.1, U10.45 (X1), Y7.1
unnamed: C81.1, R45.2, U10.44 (X2), Y7.3
unnamed: R48.2, U12.D5 (BOOT0)
unnamed: C92.2, U12.E1 (NRST)
unnamed: C105.1, U12.A1 (PC14), Y9.1
unnamed: C107.1, U12.B1 (PC15), Y9.2
unnamed: C88.1, U12.C1 (PH0), Y8.1
unnamed: C86.1, U12.D1 (PH1), Y8.3
unnamed: C106.2, R49.2, R50.1, U13.8 (FB1)
unnamed: C108.2, C109.1, R51.2, R52.1, U13.11 (FB2)
unnamed: R53.2, R54.1, U13.21 (FBL1)
unnamed: L3.1, U13.5 (SW1)
unnamed: L4.1, U13.14 (SW2)
unnamed: R55.2, U14.3 (CE)
unnamed: R56.2, U15.11 (DIR), U17.8 (SEL)
unnamed: R62.1, U15.5 (VBUS_DET)
unnamed: R61.2, U16.3 (CE)
unnamed: C117.1, U17.6 (SSBX)
unnamed: C118.1, U17.7 (SSBY)
